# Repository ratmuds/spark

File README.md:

# spark

an electronic multitool in the shape of a card

# Features

- dual RP2350As (one logic analyzer & power, other LVGL & inputs)
- 8 channel logic analyzer
- very slow ADC
- GPIO
- up to 20V 3A power output

# Files

- `/case`: The CAD for the case for the PCB. Includes a Fusion archive file, step, and stl file
- `/firmware`: Includes the firmware for both MCUs for this project. `/main` is in Rust and handles the logic analyzer, and `/secondary` is the input and LVGL C files
- `/PCB`: The PCB files for this project. The producton/gerber files are in `/production`
- `/media`: The screenshots/renders

## More Screenshots

## Bill of Materials

You can also view the BOM in `BOM.csv`

| Name                   | Description                                                           | Link                                                                     |
| ---------------------- | --------------------------------------------------------------------- | ------------------------------------------------------------------------ |
| RP2350A                | Dual-core ARM Cortex-M33 / RISC-V microcontroller 30 GPIO QFN-60 (x2) | https://jlcpcb.com/partdetail/RaspberryPi-RP2350A/C42411118              |
| W25Q128JVSIQ           | 128Mbit SPI NOR Flash SOIC-8 (x2)                                     | https://jlcpcb.com/partdetail/WinbondElec-W25Q128JVSIQ/C97521            |
| APS6404L-SQN-SN        | 64Mbit QSPI PSRAM SOP-8 (x1)                                          | https://jlcpcb.com/partdetail/APMemory-APS6404L_SQNSN/C5360304           |
| INA226AIDGSR           | 36V 16-bit I2C Power Monitor TSSOP-10 (x2)                            | https://jlcpcb.com/partdetail/TexasInstruments-INA226AIDGSR/C49851       |
| SN74LVC8T245PWR        | 8-bit dual-supply level shifter TSSOP-24 (x2)                         | https://jlcpcb.com/partdetail/TexasInstruments-SN74LVC8T245PWR/C27643    |
| IP2721                 | USB PD sink controller TSSOP-16 (x1)                                  | https://jlcpcb.com/partdetail/INJOINIC-IP2721/C603176                    |
| MP8859GQ-0000-Z        | Programmable synchronous buck converter QFN-16 (x1)                   | https://jlcpcb.com/partdetail/MPS-MP8859GQ_0000Z/C5439043                |
| SL2.1A                 | 4-port USB 2.0 hub controller SO-16 (x1)                              | https://jlcpcb.com/partdetail/Corechips-SL21A/C192893                    |
| TPS26630RGER           | 45V 5.5A eFuse with reverse polarity VQFN-24 (x2)                     | https://jlcpcb.com/partdetail/TexasInstruments-TPS26630RGER/C1850276     |
| USBLC6-2P6             | USB ESD protection SOT-666 (x1)                                       | https://jlcpcb.com/partdetail/STMicroelectronics-USBLC62P6/C15999        |
| AP63203WU-7            | 3.3V 2A synchronous buck converter TSOT-23-6 (x1)                     | https://jlcpcb.com/partdetail/DiodesIncorporated-AP63203WU7/C780769      |
| ABM8-272-T3            | 12MHz crystal oscillator RPi recommended SMD (x3)                     | https://jlcpcb.com/partdetail/AbraconLlc-ABM8_272T3/C20625731            |
| AOTA-B201610S3R3-101-T | 3.3uH polarised inductor for RP2350 DVDD SMPS 2016 (x2)               | https://jlcpcb.com/partdetail/AbraconLlc-AOTA_B201610S3R3_101T/C42411119 |
| SRP4020TA-4R7M         | 4.7uH 2.6A shielded power inductor for MP8859 (x1)                    | https://jlcpcb.com/partdetail/BOURNS-SRP4020TA4R7M/C2041623              |
| SPM6530T-4R7M          | 4.7uH TDK power inductor for USB PD path (x1)                         | https://jlcpcb.com/parts/componentSearch?searchTxt=SPM6530T-4R7M         |
| STT6N3LLH6             | N-channel 30V 6A MOSFET SOT-23-6 (x2)                                 | https://jlcpcb.com/partdetail/C3021100                                   |
| BSS138                 | N-channel 50V 0.2A logic-level MOSFET SOT-23 (x2)                     | https://jlcpcb.com/partdetail/Onsemi-BSS138/C52895                       |
| BAT54W                 | 30V 200mA dual Schottky diode SOT-323 (x4)                            | https://jlcpcb.com/partdetail/ZRE-BAT54W/C779673                         |
| BAT54S                 | 30V 200mA dual Schottky diode SOT-23 (x1)                             | https://jlcpcb.com/partdetail/hongjiacheng-BAT54S/C7420333               |
| PESD5V0U1BL            | 5V ESD protection diode SOD-882 (x19)                                 | https://jlcpcb.com/partdetail/TECHPUBLIC-PESD5V0U1BL/C2827663            |
| 1206L050YR             | 6V 0.5A/1A resettable fuse 1206 (x1)                                  | https://jlcpcb.com/parts/componentSearch?searchTxt=1206L050YR            |
| TYPE-C-31-M-12         | USB Type-C receptacle SMD 16-pin (x2)                                 | https://jlcpcb.com/partdetail/Korean_HropartsElec-TYPE_C_31_M12/C165948  |
| RLS12FTCR020           | 20mΩ 1W current sense resistor 1206 (x2)                              | https://jlcpcb.com/parts/componentSearch?searchTxt=RLS12FTCR020          |
| 0402WGF1003TCE         | 100kΩ 1% 0402 resistor (x5)                                           | https://jlcpcb.com/partdetail/UniOhm-0402WGF1003TCE/C25803               |
| 0402WGF5101TCE         | 5.1kΩ 1% 0402 resistor for USB CC (x2)                                | https://jlcpcb.com/partdetail/UniOhm-0402WGF5101TCE/C27091               |
| 0402WGF470JTCE         | 47Ω 5% 0402 resistor (x16)                                            | https://jlcpcb.com/partdetail/UniOhm-0402WGF470JTCE/C25900               |
| 0402WGF1502TCE         | 15kΩ 1% 0402 resistor (x1)                                            | https://jlcpcb.com/partdetail/UniOhm-0402WGF1502TCE/C25749               |
| 0402WGF4701TCE         | 4.7kΩ 1% 0402 resistor (x6)                                           | https://jlcpcb.com/partdetail/UniOhm-0402WGF4701TCE/C25905               |
| 0402WGF2202TCE         | 22kΩ 1% 0402 resistor (x1)                                            | https://jlcpcb.com/partdetail/UniOhm-0402WGF2202TCE/C25888               |
| 0402WGF0000TCE         | 0Ω 0402 jumper resistor (x3)                                          | https://jlcpcb.com/partdetail/UniOhm-0402WGF0000TCE/C17168               |
| 0402WGF1002TCE         | 10kΩ 1% 0402 resistor (x7)                                            | https://jlcpcb.com/partdetail/UniOhm-0402WGF1002TCE/C25744               |
| 0402WGF1001TCE         | 1kΩ 1% 0402 resistor (x4)                                             | https://jlcpcb.com/partdetail/UniOhm-0402WGF1001TCE/C21190               |
| 0603WAF6201T5E         | 6.2kΩ 1% 0603 resistor ILIM for TPS26630 (x1)                         | https://jlcpcb.com/parts/componentSearch?searchTxt=0603WAF6201T5E        |
| 0402WGF4703TCE         | 470kΩ 1% 0402 resistor UVLO divider (x1)                              | https://jlcpcb.com/partdetail/26533-0402WGF4703TCE/C25790                |
| 0402WGF2402TCE         | 24kΩ 1% 0402 resistor UVLO divider (x3)                               | https://jlcpcb.com/partdetail/UniOhm-0402WGF2402TCE/C25769               |
| 0603WAF1603T5E         | 160kΩ 1% 0603 resistor UVLO network (x1)                              | https://jlcpcb.com/partdetail/UniOhm-0603WAF1603T5E/C22813               |
| FRC0603F3571TS         | 3.57kΩ 1% 0603 resistor ILIM for TPS26630 (x1)                        | https://jlcpcb.com/partdetail/C2933206                                   |
| 0402WGF1503TCE         | 150kΩ 1% 0402 resistor PGTH divider (x1)                              | https://jlcpcb.com/partdetail/UniOhm-0402WGF1503TCE/C25755               |
| 0402WGF8201TCE         | 8.2kΩ 1% 0402 resistor ADC input protection (x1)                      | https://jlcpcb.com/partdetail/UniOhm-0402WGF8201TCE/C25924               |
| 0402WGF3303TCE         | 330kΩ 1% 0402 resistor UVLO network (x1)                              | https://jlcpcb.com/partdetail/UniOhm-0402WGF3303TCE/C25778               |
| 0402WGF3003TCE         | 300kΩ 1% 0402 resistor OVP divider (x1)                               | https://jlcpcb.com/partdetail/UniOhm-0402WGF3003TCE/C25774               |
| 0402WGF330JTCE         | 33Ω 5% 0402 resistor USB D+/D- (x2)                                   | https://jlcpcb.com/partdetail/UniOhm-0402WGF330JTCE/C25105               |
| 0603WAF270JT5E         | 27Ω 5% 0603 resistor USB D+/D- (x4)                                   | https://jlcpcb.com/partdetail/UniOhm-0603WAF270JT5E/C25190               |
| CL05B104KB54PNC        | 100nF 50V X7R 0402 decoupling capacitor (x38)                         | https://jlcpcb.com/parts/componentSearch?searchTxt=CL05B104KB54PNC       |
| CL05A105KA5NQNC        | 1uF 25V X5R 0402 capacitor (x7)                                       | https://jlcpcb.com/parts/componentSearch?searchTxt=CL05A105KA5NQNC       |
| C3216X5R1E476MTJ00E    | 47uF 25V X5R 1206 bulk capacitor (x6)                                 | https://jlcpcb.com/parts/componentSearch?searchTxt=C3216X5R1E476MTJ00E   |
| CGA2B2X7R1E223KT0Y0F   | 22uF 25V X7R 0402 capacitor (x1)                                      | https://jlcpcb.com/parts/componentSearch?searchTxt=CGA2B2X7R1E223KT0Y0F  |
| 0402CG101J500NT        | 100pF C0G/NP0 0402 capacitor (x1)                                     | https://jlcpcb.com/parts/componentSearch?searchTxt=0402CG101J500NT       |
| 0402B223K500NT         | 22nF 50V 0402 capacitor (x1)                                          | https://jlcpcb.com/parts/componentSearch?searchTxt=0402B223K500NT        |
| CL21A106KAYNNNE        | 10uF 25V X5R 0805 capacitor (x7)                                      | https://jlcpcb.com/parts/componentSearch?searchTxt=CL21A106KAYNNNE       |
| CL21A226MAQNNNE        | 22uF 25V X5R 0805 capacitor (x2)                                      | https://jlcpcb.com/parts/componentSearch?searchTxt=CL21A226MAQNNNE       |
| CL05A475MP5NRNC        | 4.7uF 10V X5R 0402 capacitor (x8)                                     | https://jlcpcb.com/parts/componentSearch?searchTxt=CL05A475MP5NRNC       |
| 0402CG150J500NT        | 15pF 50V C0G/NP0 0402 crystal load capacitor (x4)                     | https://jlcpcb.com/parts/componentSearch?searchTxt=0402CG150J500NT       |

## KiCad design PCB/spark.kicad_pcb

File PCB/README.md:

# PCB

The PCB files for this project. The gerber and other PCBA files are in the `production` folder.

This PCB was made using **KiCad 10**, and took around **40 hours** to make.

## PCB Design Screenshots

## Schematic Screenshots

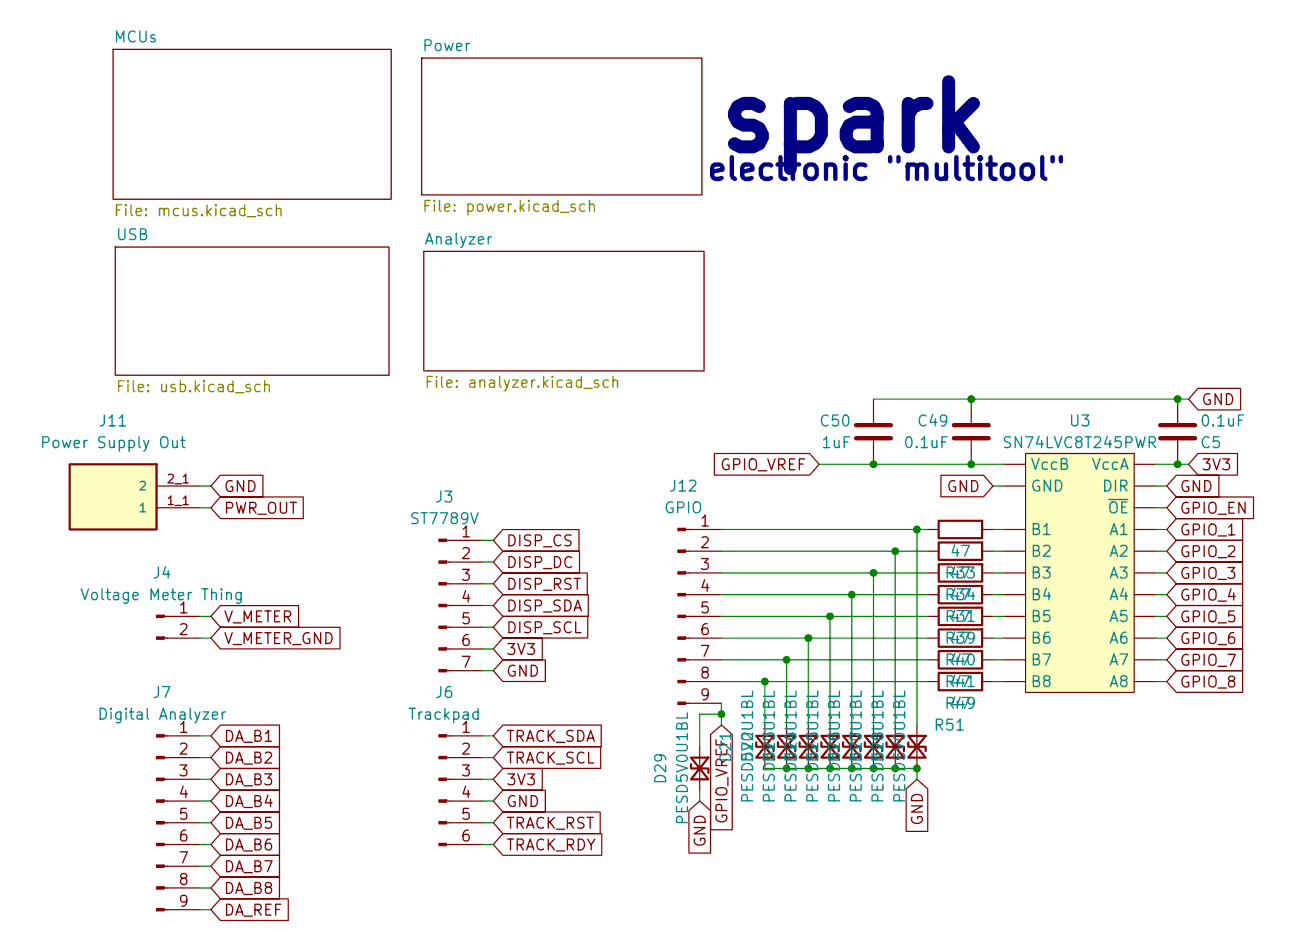
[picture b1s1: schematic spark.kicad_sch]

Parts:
C5, C49: 0.1uF; C_0402_1005Metric; MPN CL05B104KB54PNC
C50: 1uF; C_0402_1005Metric; MPN CL05A105KA5NQNC
D21, D22, D23, D24, D25, D26, D27, D28, D29: PESD5V0U1BL; D_SOD-882; MPN PESD5V0U1BL
J3: ST7789V; ST7789V Display Breakout
J4: Voltage Meter Thing; PinHeader_1x02_P2.54mm_Vertical
J6: Trackpad; SMD_Conn_01x07
J7: Digital Analyzer; PinHeader_1x09_P2.54mm_Vertical
J11: Power Supply Out; WAGO_2060-452_998-404; PARTREV N/A
J12: GPIO; PinHeader_1x09_P2.54mm_Vertical
R31, R33, R34, R39, R40, R41, R49, R51: 47; R_0402_1005Metric; MPN 0402WGF470JTCE
U3: SN74LVC8T245PWR; SOP65P640X120-24N; MPN SN74LVC8T245PWR; LCSC C27643

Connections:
3V3: C5.2, J3.6, J6.3, U3.1 (VccA); also elsewhere on the board
DA_B1: J7.1; also elsewhere on the board
DA_B2: J7.2; also elsewhere on the board
DA_B3: J7.3; also elsewhere on the board
DA_B4: J7.4; also elsewhere on the board
DA_B5: J7.5; also elsewhere on the board
DA_B6: J7.6; also elsewhere on the board
DA_B7: J7.7; also elsewhere on the board
DA_B8: J7.8; also elsewhere on the board
DA_REF: J7.9; also elsewhere on the board
DISP_CS: J3.1; also elsewhere on the board
DISP_DC: J3.2; also elsewhere on the board
DISP_RST: J3.3; also elsewhere on the board
DISP_SCL: J3.5; also elsewhere on the board
DISP_SDA: J3.4; also elsewhere on the board
GND: C5.1, C49.2, C50.2, D21.2 (A2), D22.2 (A2), D23.2 (A2), D24.2 (A2), D25.2 (A2), D26.2 (A2), D27.2 (A2), D28.2 (A2), D29.2 (A2), J3.7, J6.4, J11.2_1 (2), J11.2_2 (2), U3.2 (DIR), U3.11 (GND), U3.12 (GND), U3.13 (GND); also elsewhere on the board
GPIO_1: U3.3 (A1); also elsewhere on the board
GPIO_2: U3.4 (A2); also elsewhere on the board
GPIO_3: U3.5 (A3); also elsewhere on the board
GPIO_4: U3.6 (A4); also elsewhere on the board
GPIO_5: U3.7 (A5); also elsewhere on the board
GPIO_6: U3.8 (A6); also elsewhere on the board
GPIO_7: U3.9 (A7); also elsewhere on the board
GPIO_8: U3.10 (A8); also elsewhere on the board
GPIO_EN: U3.22 (~OE); also elsewhere on the board
GPIO_VREF: C49.1, C50.1, D29.1 (A1), J12.9, U3.23 (VccB), U3.24 (VccB)
unnamed: D21.1 (A1), J12.8, R51.1
unnamed: D22.1 (A1), J12.7, R49.1
unnamed: D23.1 (A1), J12.6, R41.1
unnamed: D24.1 (A1), J12.5, R40.1
unnamed: D25.1 (A1), J12.4, R39.1
unnamed: D26.1 (A1), J12.3, R31.1
unnamed: D27.1 (A1), J12.2, R34.1
unnamed: D28.1 (A1), J12.1, R33.1
unnamed: R33.2, U3.21 (B1)
unnamed: R34.2, U3.20 (B2)
unnamed: R31.2, U3.19 (B3)
unnamed: R39.2, U3.18 (B4)
unnamed: R40.2, U3.17 (B5)
unnamed: R41.2, U3.16 (B6)
unnamed: R49.2, U3.15 (B7)
unnamed: R51.2, U3.14 (B8)
PWR_OUT: J11.1_1 (1), J11.1_2 (1); also elsewhere on the board
TRACK_RDY: J6.6; also elsewhere on the board
TRACK_RST: J6.5; also elsewhere on the board
TRACK_SCL: J6.2; also elsewhere on the board
TRACK_SDA: J6.1; also elsewhere on the board
V_METER: J4.1; also elsewhere on the board
V_METER_GND: J4.2; also elsewhere on the board

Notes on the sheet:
spark
electronic "multitool"

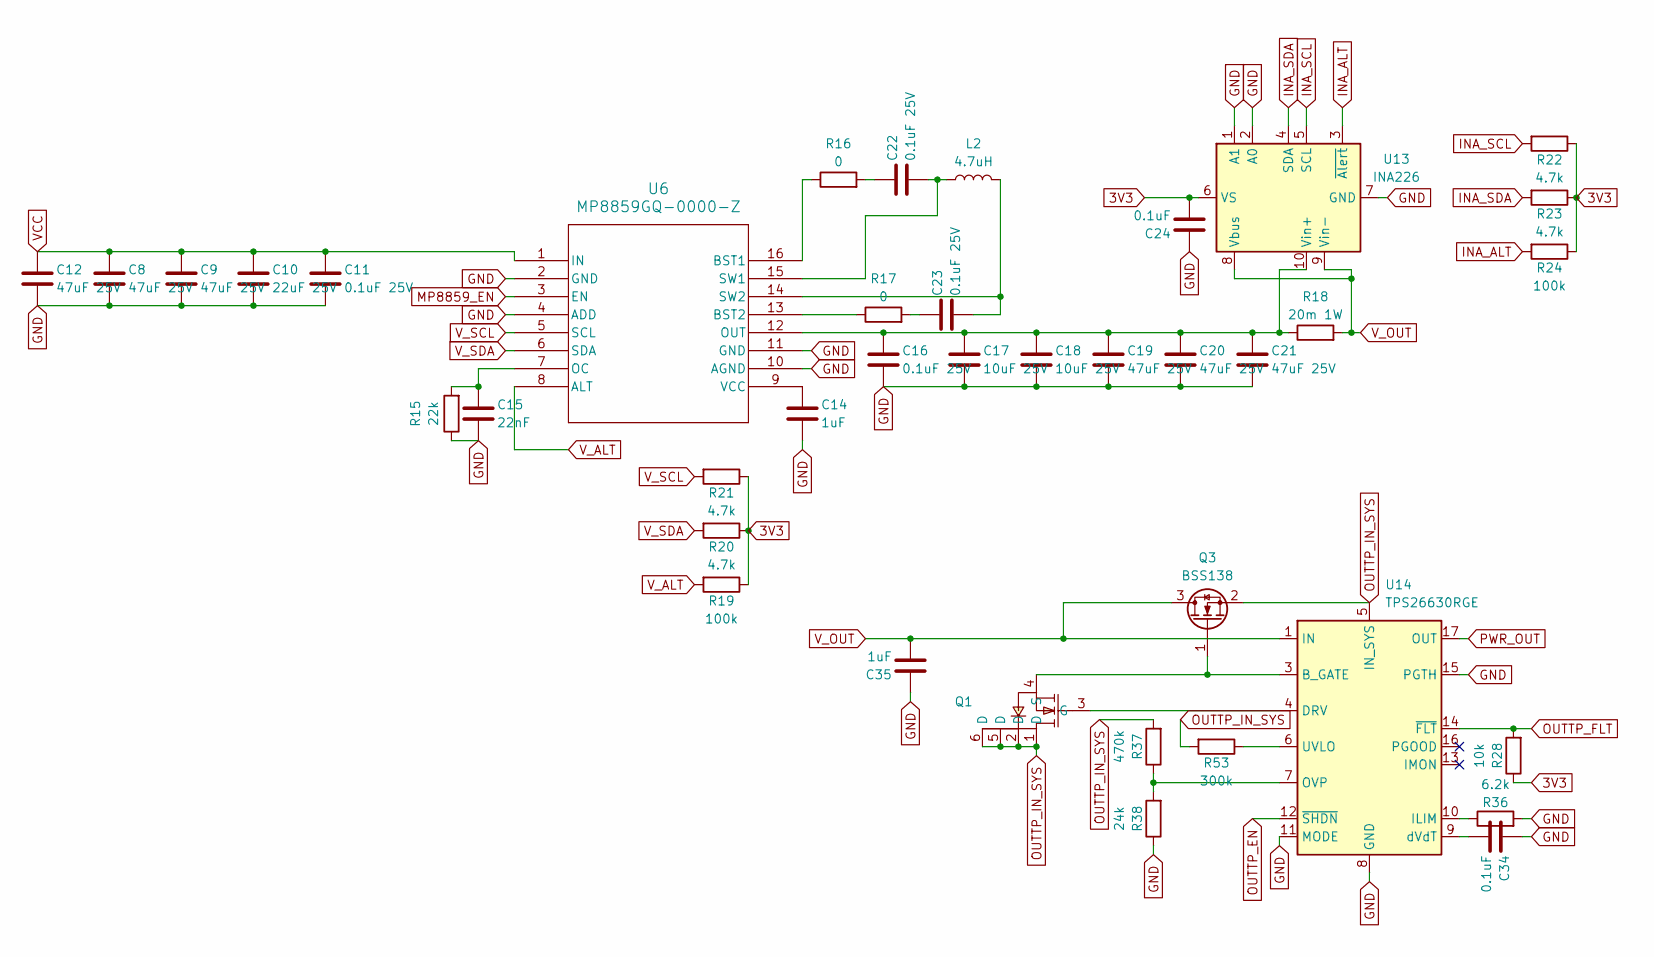
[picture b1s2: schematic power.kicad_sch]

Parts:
C8, C9, C12, C19, C20, C21: 47uF 25V; C_1206_3216Metric; MPN C3216X5R1E476MTJ00E
C10: 22uF 25V; C_0805_2012Metric; MPN CL21A226MAQNNNE
C11, C16, C22, C23: 0.1uF 25V; C_0402_1005Metric; MPN CL05B104KB54PNC
C14, C35: 1uF; C_0402_1005Metric; MPN CL05A105KA5NQNC
C15: 22nF; C_0402_1005Metric; MPN 0402B223K500NT
C17, C18: 10uF 25V; C_0805_2012Metric; MPN CL21A106KAYNNNE
C24, C34: 0.1uF; C_0402_1005Metric; MPN CL05B104KB54PNC
L2: 4.7uH; IND_SPM6530T-4R7M; MPN SPM6530T-4R7M
Q1: STT6N3LLH6_C3021100; SOT-23-6_L2.9-W1.6-P0.95-LS2.8-BR; MPN STT6N3LLH6; LCSC Part C3021100
Q3: BSS138; SOT-23; MPN BSS138
R15: 22k; R_0402_1005Metric; MPN 0402WGF2202TCE
R16, R17: 0; R_0402_1005Metric; MPN 0402WGF0000TCE
R18: 20m 1W; R_1206_3216Metric; MPN RLS12FTCR020
R19, R24: 100k; R_0402_1005Metric; MPN 0402WGF1003TCE
R20, R21, R22, R23: 4.7k; R_0402_1005Metric; MPN 0402WGF4701TCE
R28: 10k; R_0402_1005Metric; MPN 0402WGF1002TCE
R36: 6.2k; R_0603_1608Metric; MPN 0603WAF6201T5E
R37: 470k; R_0402_1005Metric; MPN 0402WGF4703TCE
R38: 24k; R_0402_1005Metric; MPN 0402WGF2402TCE
R53: 300k; R_0402_1005Metric; MPN 0402WGF3003TCE
U6: MP8859GQ-0000-Z; QFN-16_MP8859_00_MNP; MPN MP8859GQ-0000-Z
U13: INA226; TSSOP-10_3x3mm_P0.5mm; MPN INA226AIDGSR
U14: TPS26630RGE; Texas_RGE0024H_VQFN-24-1EP_4x4mm_P0.5mm_EP2.7x2.7mm_Thermal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; MPN TPS26630RGER

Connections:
3V3: C24.1, R19.1, R20.1, R21.1, R22.1, R23.1, R24.1, R28.1, U13.6 (VS); also elsewhere on the board
GND: C8.1, C9.1, C10.1, C11.1, C12.1, C14.1, C15.1, C16.1, C17.1, C18.1, C19.1, C20.1, C21.1, C24.2, C34.2, C35.2, R15.1, R36.2, R38.1, U6.2 (GND), U6.4 (ADD), U6.10 (AGND), U6.11 (GND), U13.1 (A1), U13.2 (A0), U13.7 (GND), U14.8 (GND), U14.11 (MODE), U14.15 (PGTH), U14.25 (GND); also elsewhere on the board
INA_ALT: R24.2, U13.3 (~Alert); also elsewhere on the board
INA_SCL: R22.2, U13.5 (SCL); also elsewhere on the board
INA_SDA: R23.2, U13.4 (SDA); also elsewhere on the board
MP8859_EN: U6.3 (EN); also elsewhere on the board
unnamed: C22.2, R16.2
unnamed: C23.2, R17.2
unnamed: Q1.3 (G), U14.4 (DRV)
unnamed: Q1.4 (S), Q3.1 (G), U14.3 (B_GATE)
unnamed: R16.1, U6.16 (BST1)
unnamed: R17.1, U6.13 (BST2)
unnamed: C15.2, R15.2, U6.7 (OC)
unnamed: C22.1, L2.1, U6.15 (SW1)
unnamed: C23.1, L2.2, U6.14 (SW2)
unnamed: C14.2, U6.9 (VCC)
unnamed: C16.2, C17.2, C18.2, C19.2, C20.2, C21.2, R18.1, U6.12 (OUT), U13.10 (Vin+)
unnamed: R36.1, U14.10 (ILIM)
unnamed: R37.1, R38.2, U14.7 (OVP)
unnamed: R53.1, U14.6 (UVLO)
unnamed: C34.1, U14.9 (dVdT)
OUTTP_EN: U14.12 (~SHDN); also elsewhere on the board
OUTTP_FLT: R28.2, U14.14 (~FLT); also elsewhere on the board
OUTTP_IN_SYS: Q1.1 (D), Q1.2 (D), Q1.5 (D), Q1.6 (D), Q3.2 (S), R37.2, R53.2, U14.5 (IN_SYS)
PWR_OUT: U14.17 (OUT), U14.18 (OUT); also elsewhere on the board
VCC: C8.2, C9.2, C10.2, C11.2, C12.2, U6.1 (IN); also elsewhere on the board
V_ALT: R19.2, U6.8 (ALT); also elsewhere on the board
V_OUT: C35.1, Q3.3 (D), R18.2, U13.8 (Vbus), U13.9 (Vin-), U14.1 (IN), U14.2 (IN)
V_SCL: R21.2, U6.5 (SCL); also elsewhere on the board
V_SDA: R20.2, U6.6 (SDA); also elsewhere on the board

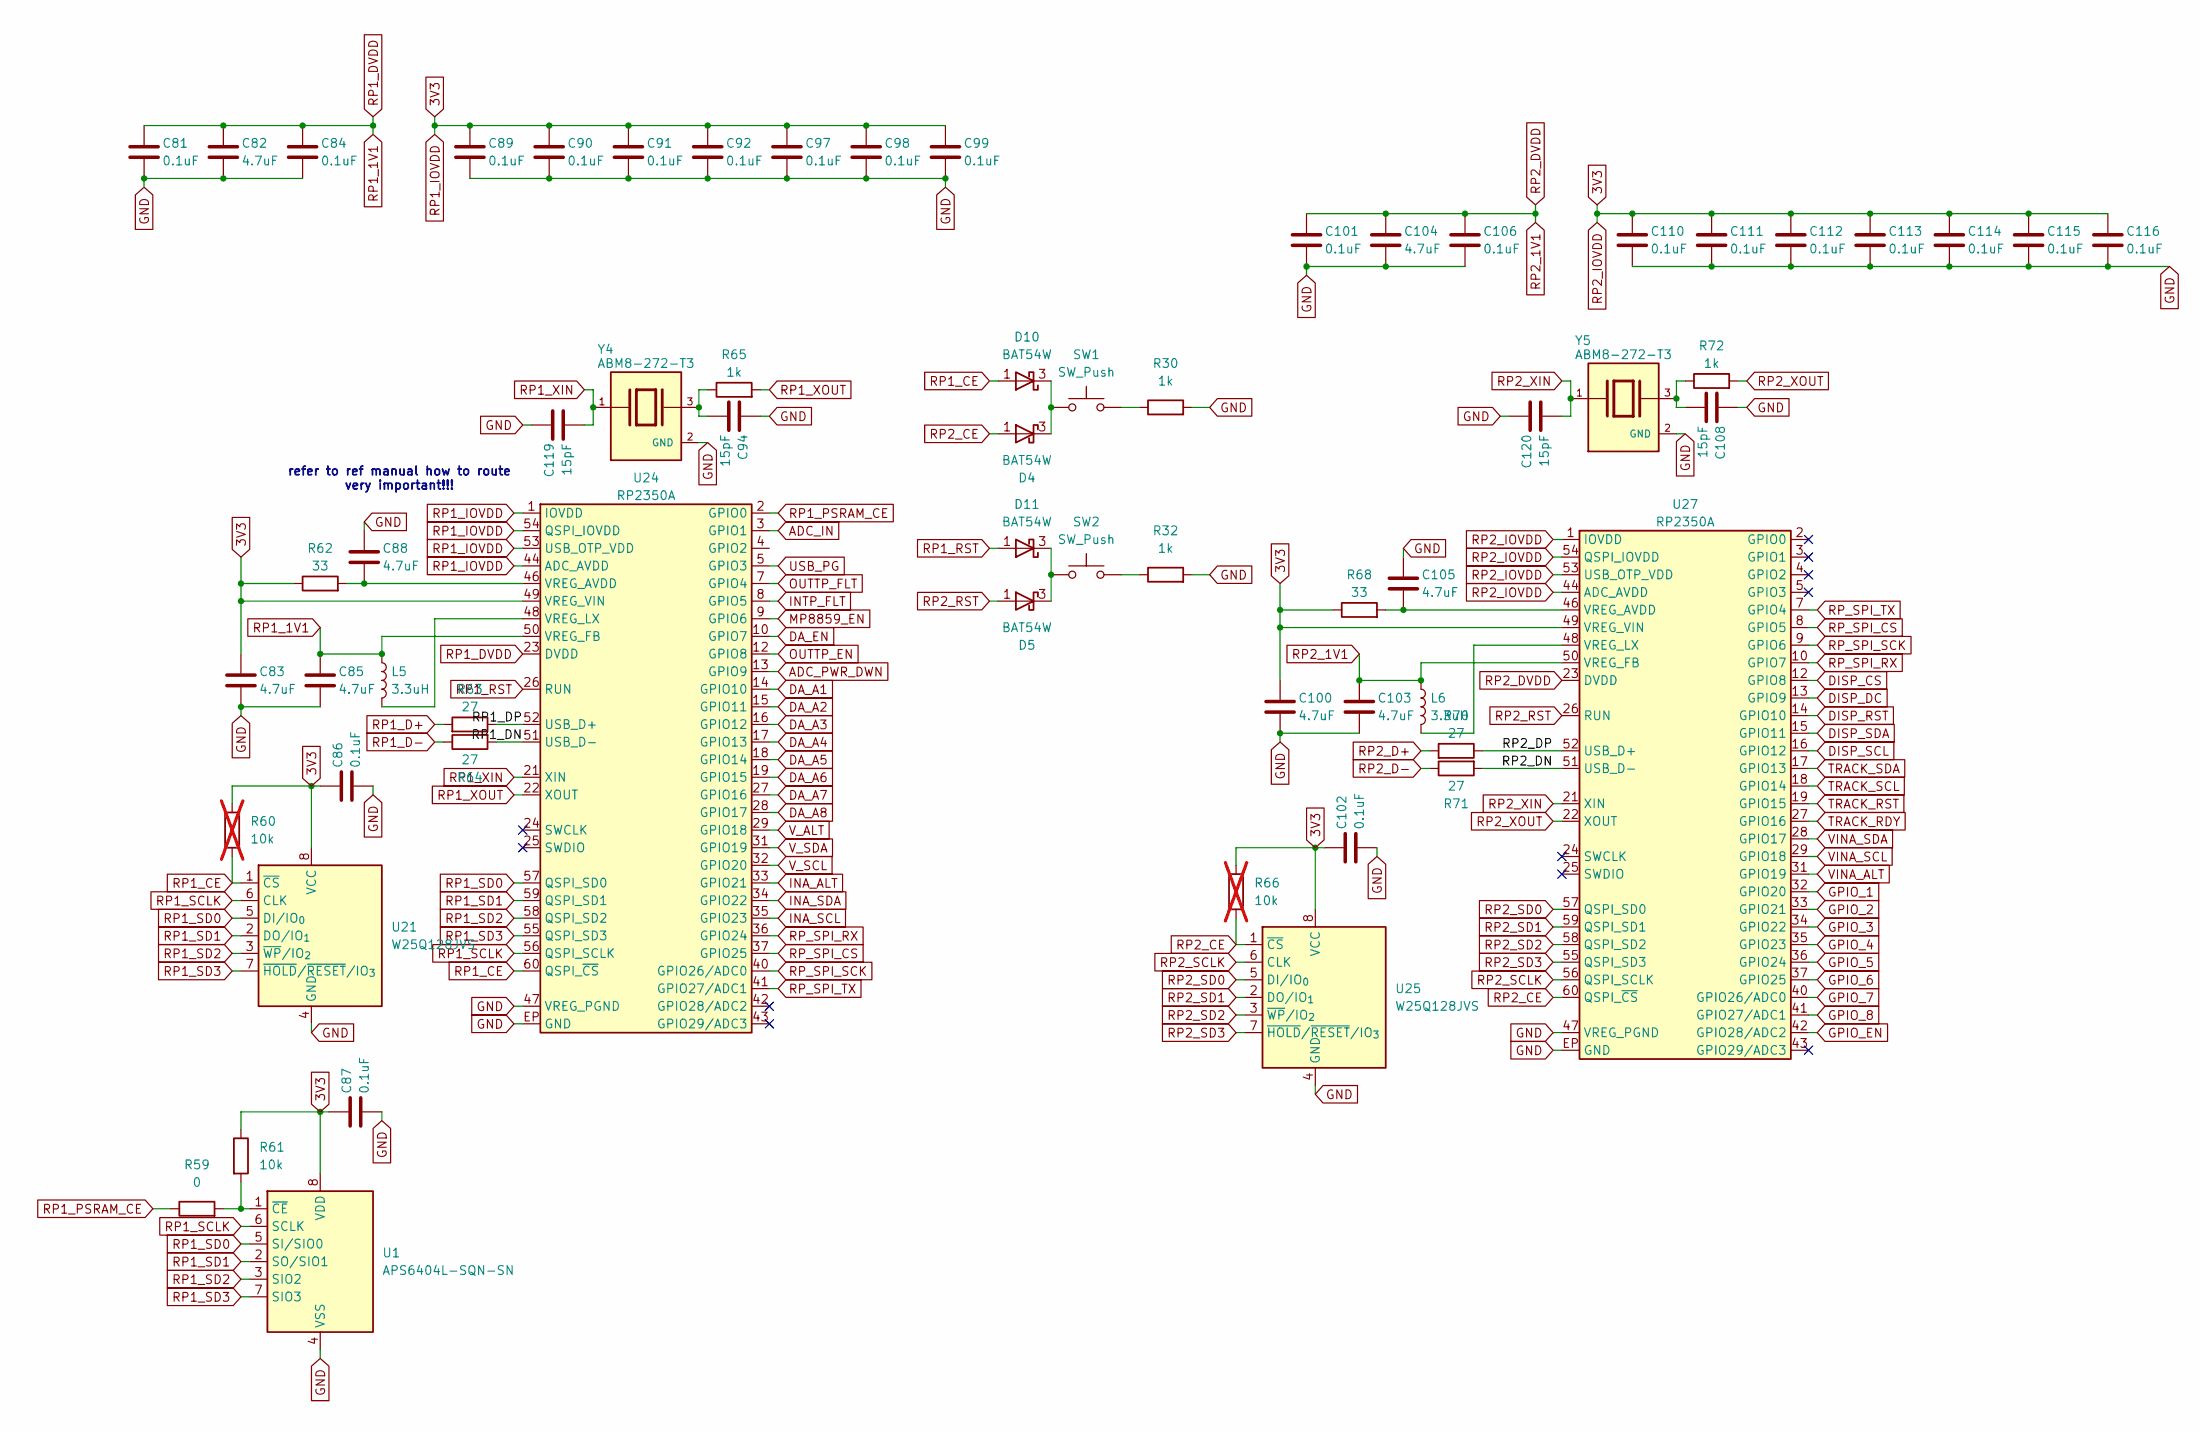
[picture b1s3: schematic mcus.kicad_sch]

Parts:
C81, C84, C86, C87, C89, C90, C91, C92, C97, C98, C99, C101, C102, C106, C110, C111, C112, C113, C114, C115, C116: 0.1uF; C_0402_1005Metric; MPN CL05B104KB54PNC
C82, C83, C85, C88, C100, C103, C104, C105: 4.7uF; C_0402_1005Metric; MPN CL05A475MP5NRNC
C94, C108, C119, C120: 15pF; C_0402_1005Metric; MPN 0402CG150J500NT
D4, D5, D10, D11: BAT54W; SOT-323_SC-70; MPN BAT54W
L5, L6: 3.3uH; AOTA-B201610S3R3-101-T; MPN AOTA-B201610S3R3-101-T
R30, R32, R65, R72: 1k; R_0402_1005Metric; MPN 0402WGF1001TCE
R59: 0; R_0402_1005Metric; MPN 0402WGF0000TCE
R60, R66: 10k; R_0402_1005Metric; MPN 0402WGF1002TCE; not fitted
R61: 10k; R_0402_1005Metric; MPN 0402WGF1002TCE
R62, R68: 33; R_0402_1005Metric; MPN 0402WGF330JTCE
R63, R64, R70, R71: 27; R_0603_1608Metric; MPN 0603WAF270JT5E
SW1, SW2: SW_Push; SW_TS-1088-AR02016; MPN TS-1088-AR02016
U1: APS6404L-SQN-SN; SOP-8_L4.9-W3.9-P1.27-LS6.0-BL; MPN APS6404L-SQN-SN
U21, U25: W25Q128JVS; SOIC-8_5.3x5.3mm_P1.27mm; MPN W25Q128JVSIQ
U24, U27: RP2350A; QFN-60-1EP_7x7mm_P0.4mm_EP3.4x3.4mm_ThermalVias; MPN RP2350A
Y4, Y5: ABM8-272-T3; XTAL_ABM8-272-T3; PARTREV 07-29-20

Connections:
3V3: C83.2, C86.2, C87.2, C89.2, C90.2, C91.2, C92.2, C97.2, C98.2, C99.2, C100.2, C102.2, C110.2, C111.2, C112.2, C113.2, C114.2, C115.2, C116.2, R60.1, R61.1, R62.1, R66.1, R68.1, U1.8 (VDD), U21.8 (VCC), U24.1 (IOVDD), U24.11 (IOVDD), U24.20 (IOVDD), U24.30 (IOVDD), U24.38 (IOVDD), U24.44 (ADC_AVDD), U24.45 (IOVDD), U24.49 (VREG_VIN), U24.53 (USB_OTP_VDD), U24.54 (QSPI_IOVDD), U25.8 (VCC), U27.1 (IOVDD), U27.11 (IOVDD), U27.20 (IOVDD), U27.30 (IOVDD), U27.38 (IOVDD), U27.44 (ADC_AVDD), U27.45 (IOVDD), U27.49 (VREG_VIN), U27.53 (USB_OTP_VDD), U27.54 (QSPI_IOVDD); also elsewhere on the board
/MCUs/RP1_DN: R64.2, U24.51 (USB_D-)
/MCUs/RP1_DP: R63.1, U24.52 (USB_D+)
/MCUs/RP2_DN: R71.2, U27.51 (USB_D-)
/MCUs/RP2_DP: R70.1, U27.52 (USB_D+)
ADC_IN: U24.3 (GPIO1); also elsewhere on the board
ADC_PWR_DWN: U24.13 (GPIO9)
DA_A1: U24.14 (GPIO10); also elsewhere on the board
DA_A2: U24.15 (GPIO11); also elsewhere on the board
DA_A3: U24.16 (GPIO12); also elsewhere on the board
DA_A4: U24.17 (GPIO13); also elsewhere on the board
DA_A5: U24.18 (GPIO14); also elsewhere on the board
DA_A6: U24.19 (GPIO15); also elsewhere on the board
DA_A7: U24.27 (GPIO16); also elsewhere on the board
DA_A8: U24.28 (GPIO17); also elsewhere on the board
DA_EN: U24.10 (GPIO7); also elsewhere on the board
DISP_CS: U27.12 (GPIO8); also elsewhere on the board
DISP_DC: U27.13 (GPIO9); also elsewhere on the board
DISP_RST: U27.14 (GPIO10); also elsewhere on the board
DISP_SCL: U27.16 (GPIO12); also elsewhere on the board
DISP_SDA: U27.15 (GPIO11); also elsewhere on the board
GND: C81.1, C82.1, C83.1, C84.1, C85.1, C86.1, C87.1, C88.2, C89.1, C90.1, C91.1, C92.1, C94.2, C97.1, C98.1, C99.1, C100.1, C101.1, C102.1, C103.1, C104.1, C105.2, C106.1, C108.2, C110.1, C111.1, C112.1, C113.1, C114.1, C115.1, C116.1, C119.2, C120.2, R30.2, R32.2, U1.4 (VSS), U21.4 (GND), U24.47 (VREG_PGND), U24.EP (GND), U25.4 (GND), U27.47 (VREG_PGND), U27.EP (GND), Y4.2 (GND), Y4.4 (GND), Y5.2 (GND), Y5.4 (GND); also elsewhere on the board
GPIO_1: U27.32 (GPIO20); also elsewhere on the board
GPIO_2: U27.33 (GPIO21); also elsewhere on the board
GPIO_3: U27.34 (GPIO22); also elsewhere on the board
GPIO_4: U27.35 (GPIO23); also elsewhere on the board
GPIO_5: U27.36 (GPIO24); also elsewhere on the board
GPIO_6: U27.37 (GPIO25); also elsewhere on the board
GPIO_7: U27.40 (GPIO26/ADC0); also elsewhere on the board
GPIO_8: U27.41 (GPIO27/ADC1); also elsewhere on the board
GPIO_EN: U27.42 (GPIO28/ADC2); also elsewhere on the board
INA_ALT: U24.33 (GPIO21); also elsewhere on the board
INA_SCL: U24.35 (GPIO23); also elsewhere on the board
INA_SDA: U24.34 (GPIO22); also elsewhere on the board
INTP_FLT: U24.8 (GPIO5); also elsewhere on the board
MP8859_EN: U24.9 (GPIO6); also elsewhere on the board
unnamed: C94.1, R65.1, Y4.3
unnamed: C108.1, R72.1, Y5.3
unnamed: D4.3 (K), D10.3 (K), SW1.1
unnamed: D5.3 (K), D11.3 (K), SW2.1
unnamed: R30.1, SW1.2
unnamed: R32.1, SW2.2
unnamed: R59.2, R61.2, U1.1 (~CE)
unnamed: C88.1, R62.2, U24.46 (VREG_AVDD)
unnamed: L5.2, U24.48 (VREG_LX)
unnamed: C105.1, R68.2, U27.46 (VREG_AVDD)
unnamed: L6.2, U27.48 (VREG_LX)
OUTTP_EN: U24.12 (GPIO8); also elsewhere on the board
OUTTP_FLT: U24.7 (GPIO4); also elsewhere on the board
RP1_1V1: C81.2, C82.2, C84.2, C85.2, L5.1, U24.6 (DVDD), U24.23 (DVDD), U24.39 (DVDD), U24.50 (VREG_FB)
RP1_CE: D10.1 (A), R60.2, U21.1 (~CS), U24.60 (QSPI_~CS)
RP1_D+: R63.2; also elsewhere on the board
RP1_D-: R64.1; also elsewhere on the board
RP1_PSRAM_CE: R59.1, U24.2 (GPIO0)
RP1_RST: D11.1 (A), U24.26 (RUN)
RP1_SCLK: U1.6 (SCLK), U21.6 (CLK), U24.56 (QSPI_SCLK)
RP1_SD0: U1.5 (SI/SIO0), U21.5 (DI/IO_{0}), U24.57 (QSPI_SD0)
RP1_SD1: U1.2 (SO/SIO1), U21.2 (DO/IO_{1}), U24.59 (QSPI_SD1)
RP1_SD2: U1.3 (SIO2), U21.3 (~WP/IO_{2}), U24.58 (QSPI_SD2)
RP1_SD3: U1.7 (SIO3), U21.7 (~HOLD/~RESET/IO_{3}), U24.55 (QSPI_SD3)
RP1_XIN: C119.1, U24.21 (XIN), Y4.1
RP1_XOUT: R65.2, U24.22 (XOUT)
RP2_1V1: C101.2, C103.2, C104.2, C106.2, L6.1, U27.6 (DVDD), U27.23 (DVDD), U27.39 (DVDD), U27.50 (VREG_FB)
RP2_CE: D4.1 (A), R66.2, U25.1 (~CS), U27.60 (QSPI_~CS)
RP2_D+: R70.2; also elsewhere on the board
RP2_D-: R71.1; also elsewhere on the board
RP2_RST: D5.1 (A), U27.26 (RUN)
RP2_SCLK: U25.6 (CLK), U27.56 (QSPI_SCLK)
RP2_SD0: U25.5 (DI/IO_{0}), U27.57 (QSPI_SD0)
RP2_SD1: U25.2 (DO/IO_{1}), U27.59 (QSPI_SD1)
RP2_SD2: U25.3 (~WP/IO_{2}), U27.58 (QSPI_SD2)
RP2_SD3: U25.7 (~HOLD/~RESET/IO_{3}), U27.55 (QSPI_SD3)
RP2_XIN: C120.1, U27.21 (XIN), Y5.1
RP2_XOUT: R72.2, U27.22 (XOUT)
RP_SPI_CS: U24.37 (GPIO25), U27.8 (GPIO5)
RP_SPI_RX: U24.36 (GPIO24), U27.10 (GPIO7)
RP_SPI_SCK: U24.40 (GPIO26/ADC0), U27.9 (GPIO6)
RP_SPI_TX: U24.41 (GPIO27/ADC1), U27.7 (GPIO4)
TRACK_RDY: U27.27 (GPIO16); also elsewhere on the board
TRACK_RST: U27.19 (GPIO15); also elsewhere on the board
TRACK_SCL: U27.18 (GPIO14); also elsewhere on the board
TRACK_SDA: U27.17 (GPIO13); also elsewhere on the board
USB_PG: U24.5 (GPIO3); also elsewhere on the board
VINA_ALT: U27.31 (GPIO19); also elsewhere on the board
VINA_SCL: U27.29 (GPIO18); also elsewhere on the board
VINA_SDA: U27.28 (GPIO17); also elsewhere on the board
V_ALT: U24.29 (GPIO18); also elsewhere on the board
V_SCL: U24.32 (GPIO20); also elsewhere on the board
V_SDA: U24.31 (GPIO19); also elsewhere on the board

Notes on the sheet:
refer to ref manual how to route very important!!!

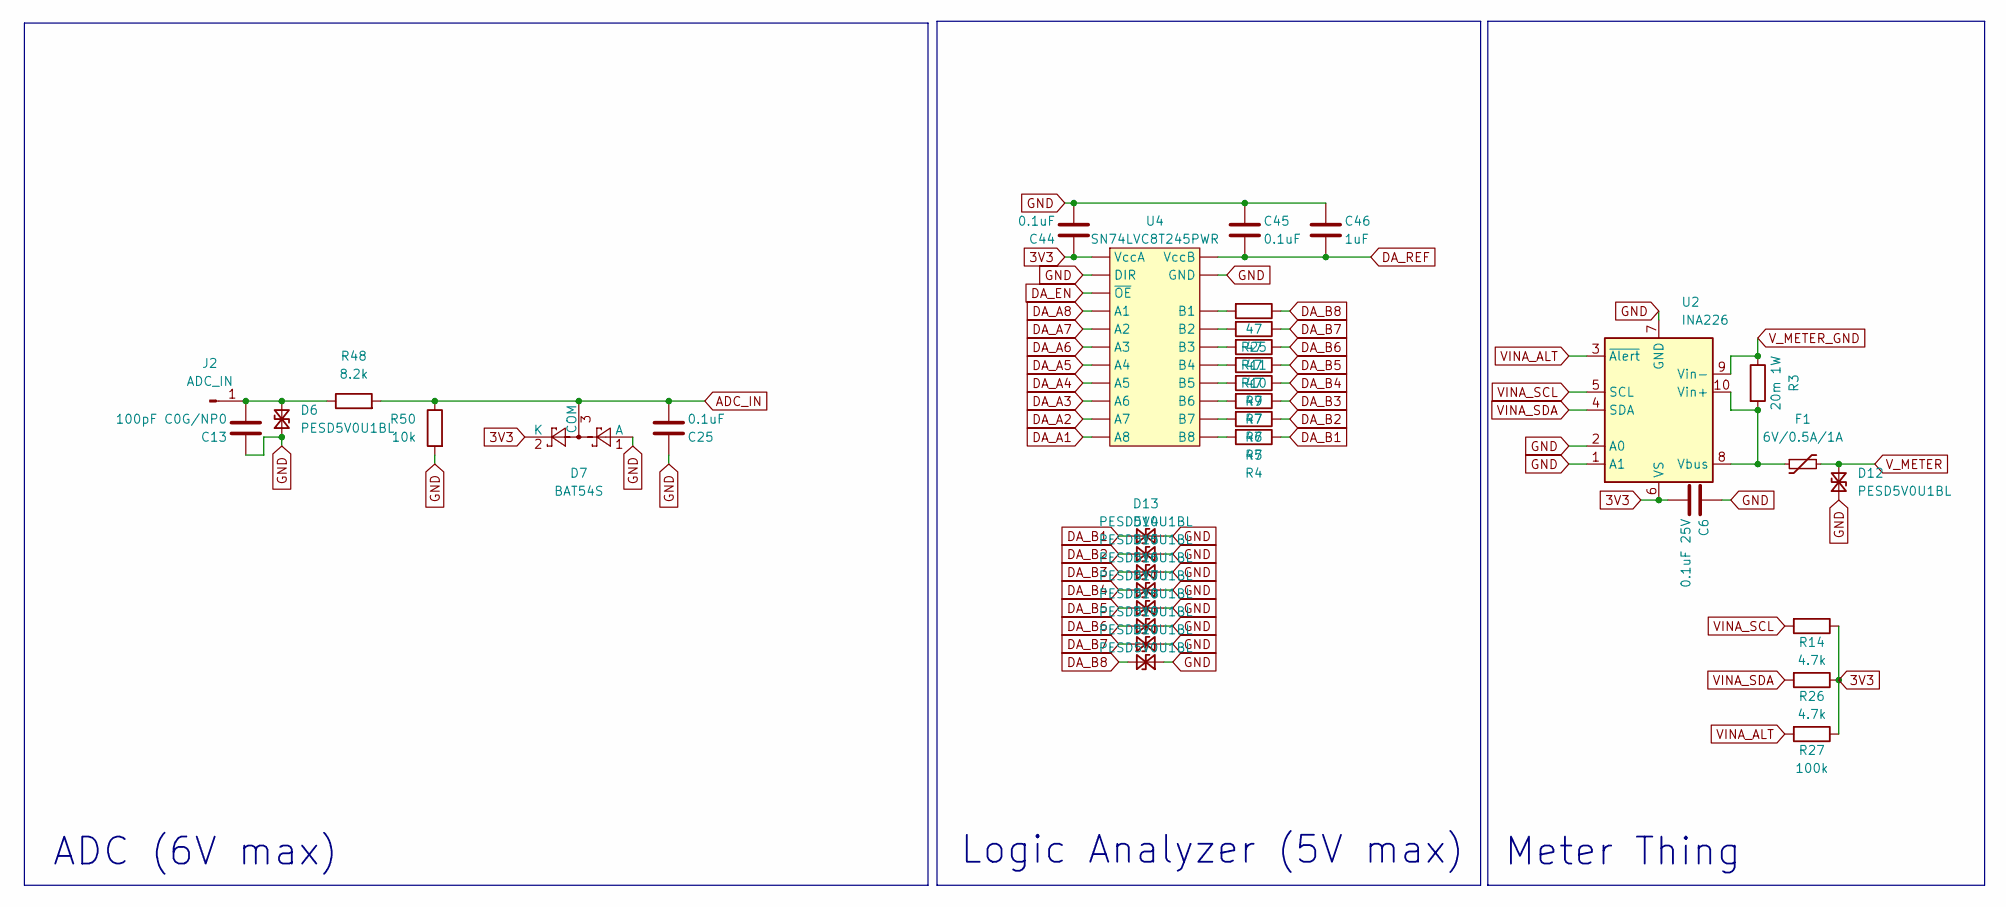
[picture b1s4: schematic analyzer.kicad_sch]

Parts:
C6: 0.1uF 25V; C_0402_1005Metric; MPN CL05B104KB54PNC
C13: 100pF C0G/NP0; C_0402_1005Metric; MPN 0402CG101J500NT
C25, C44, C45: 0.1uF; C_0402_1005Metric; MPN CL05B104KB54PNC
C46: 1uF; C_0402_1005Metric; MPN CL05A105KA5NQNC
D6, D12, D13, D14, D15, D16, D17, D18, D19, D20: PESD5V0U1BL; D_SOD-882; MPN PESD5V0U1BL
D7: BAT54S; SOT-23; MPN BAT54S
F1: 6V/0.5A/1A; 1206; MPN 1206L050YR
J2: ADC_IN; PinHeader_1x01_P2.54mm_Vertical
R3: 20m 1W; R_1206_3216Metric; MPN RLS12FTCR020
R4, R5, R6, R7, R9, R10, R11, R25: 47; R_0402_1005Metric; MPN 0402WGF470JTCE
R14, R26: 4.7k; R_0402_1005Metric; MPN 0402WGF4701TCE
R27: 100k; R_0402_1005Metric; MPN 0402WGF1003TCE
R48: 8.2k; R_0402_1005Metric; MPN 0402WGF8201TCE
R50: 10k; R_0402_1005Metric; MPN 0402WGF1002TCE
U2: INA226; TSSOP-10_3x3mm_P0.5mm; MPN INA226AIDGSR
U4: SN74LVC8T245PWR; SOP65P640X120-24N; MPN SN74LVC8T245PWR; LCSC C27643

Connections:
3V3: C6.1, C44.2, D7.2 (K), R14.1, R26.1, R27.1, U2.6 (VS), U4.1 (VccA); also elsewhere on the board
ADC_IN: C25.1, D7.3 (COM), R48.2, R50.1; also elsewhere on the board
DA_A1: U4.10 (A8); also elsewhere on the board
DA_A2: U4.9 (A7); also elsewhere on the board
DA_A3: U4.8 (A6); also elsewhere on the board
DA_A4: U4.7 (A5); also elsewhere on the board
DA_A5: U4.6 (A4); also elsewhere on the board
DA_A6: U4.5 (A3); also elsewhere on the board
DA_A7: U4.4 (A2); also elsewhere on the board
DA_A8: U4.3 (A1); also elsewhere on the board
DA_B1: D13.2 (A2), R4.1; also elsewhere on the board
DA_B2: D14.2 (A2), R5.1; also elsewhere on the board
DA_B3: D15.2 (A2), R6.1; also elsewhere on the board
DA_B4: D16.2 (A2), R7.1; also elsewhere on the board
DA_B5: D17.2 (A2), R9.1; also elsewhere on the board
DA_B6: D18.2 (A2), R10.1; also elsewhere on the board
DA_B7: D19.2 (A2), R11.1; also elsewhere on the board
DA_B8: D20.2 (A2), R25.1; also elsewhere on the board
DA_EN: U4.22 (~OE); also elsewhere on the board
DA_REF: C45.1, C46.1, U4.23 (VccB), U4.24 (VccB); also elsewhere on the board
GND: C6.2, C13.2, C25.2, C44.1, C45.2, C46.2, D6.1 (A1), D7.1 (A), D12.1 (A1), D13.1 (A1), D14.1 (A1), D15.1 (A1), D16.1 (A1), D17.1 (A1), D18.1 (A1), D19.1 (A1), D20.1 (A1), R50.2, U2.1 (A1), U2.2 (A0), U2.7 (GND), U4.2 (DIR), U4.11 (GND), U4.12 (GND), U4.13 (GND); also elsewhere on the board
unnamed: C13.1, D6.2 (A2), J2.1 (Pin_1_1), R48.1
unnamed: F1.1, R3.2, U2.8 (Vbus), U2.10 (Vin+)
unnamed: R25.2, U4.21 (B1)
unnamed: R11.2, U4.20 (B2)
unnamed: R10.2, U4.19 (B3)
unnamed: R9.2, U4.18 (B4)
unnamed: R7.2, U4.17 (B5)
unnamed: R6.2, U4.16 (B6)
unnamed: R5.2, U4.15 (B7)
unnamed: R4.2, U4.14 (B8)
VINA_ALT: R27.2, U2.3 (~Alert); also elsewhere on the board
VINA_SCL: R14.2, U2.5 (SCL); also elsewhere on the board
VINA_SDA: R26.2, U2.4 (SDA); also elsewhere on the board
V_METER: D12.2 (A2), F1.2; also elsewhere on the board
V_METER_GND: R3.1, U2.9 (Vin-); also elsewhere on the board

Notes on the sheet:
Logic Analyzer (5V max)
ADC (6V max)
Meter Thing
